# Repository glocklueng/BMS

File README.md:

# BMS
Battery management system

This is battery management system developed on University FESB for purpose of student project E-kart.
Features:
here goes features

Pic

Description

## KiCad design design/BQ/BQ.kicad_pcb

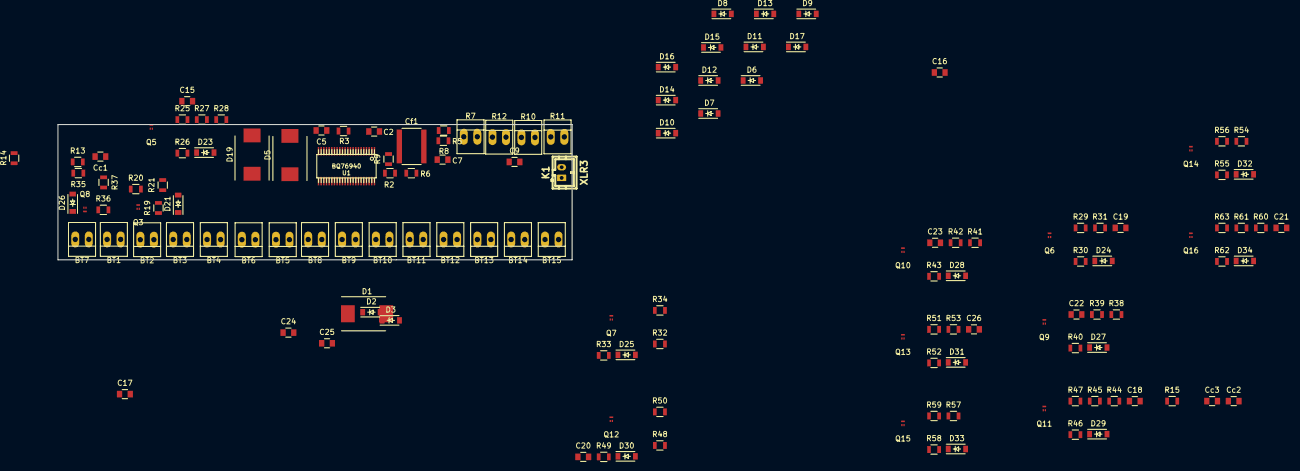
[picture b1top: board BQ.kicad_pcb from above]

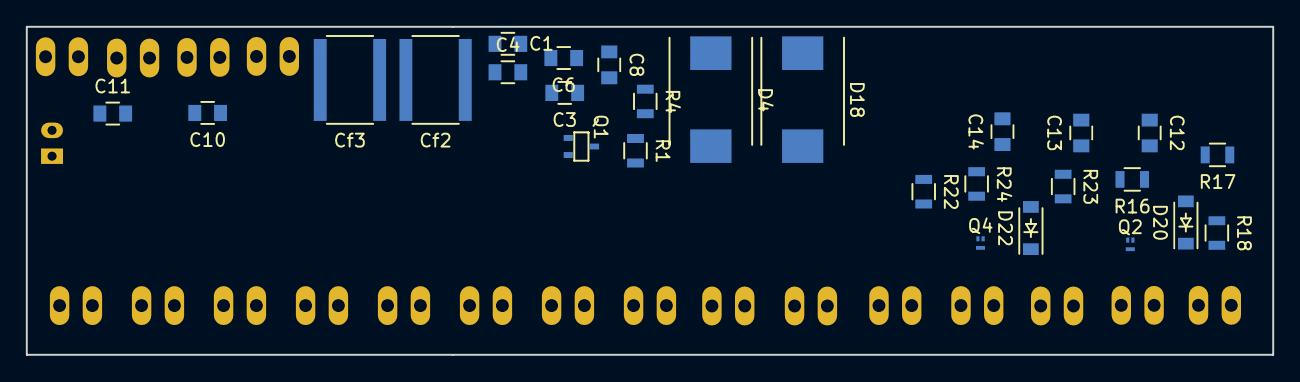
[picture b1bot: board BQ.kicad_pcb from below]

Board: 2 copper layers, 96.5 x 25.4 mm, 162 parts (27 on the bottom side), 87 nets, no tracks yet.

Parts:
BT1, BT2, BT3, BT4, BT5, BT6, BT7, BT8, BT9, BT10, BT11, BT12, BT13, BT14, BT15: BATTERY; PINHEAD1-2
C1, C9, C10, C11: 4.7; C_0805
C2, C4, C5: 1u; C_0805
C3, C6, C8: 0.1u; C_0805
C7: 4,7; C_0805
C12, C13, C14, C15, C16, C17, C18, C19, C20, C21, C22, C23, C24, C25, C26: 10u; C_0805
Cc1, Cc2: 10u; C_0805
Cc3: 1ou; C_0805
Cf1, Cf2, Cf3: 40u; C_1825
D1, D5, D18, D19: DIODE; Diode-DO-214AB
D2, D3: ZENER; SOD-123
D4: 100V; Diode-DO-214AB
D6, D7, D8, D9, D10, D11, D12, D13, D14, D15, D16, D17: DIODESCH; SOD-123
D20, D21, D22, D23, D24, D27, D28, D29, D31, D32, D33, D34: 5,6; SOD-123
D25, D26, D30: 5,6V; SOD-123
K1: XLR3; b2b-ph-kl
Q1: BST82,215; sc70
Q2, Q3, Q4, Q5, Q6, Q9, Q10, Q11, Q13, Q14, Q15, Q16: MOSFET_N; DFB1006-4
Q7, Q8, Q12: DMN2300UFB4-7B; DFB1006-4
R1: 200; R_0805
R2: 100k; R_0805
R3, R13, R14, R15, R18, R21, R24, R25, R28, R31, R34, R37, R40, R43, R44, R47, R50, R53, R56, R59, R60, R63: 1K; R_0805
R4: 100K; R_0805
R5, R6, R8: 100; R_0805
R7: SHUNT 0.001; PINHEAD1-2
R9: 300K; R_0805
R10, R11, R12: NTC 10k; PINHEAD1-2
R16, R19, R22, R26, R29, R32, R35, R38, R41, R45, R48, R51, R54, R57, R61: 50; R_0805
R17, R20, R23, R27, R30, R33, R36, R39, R42, R46, R49, R52, R55, R58, R62: 10K; R_0805
U1: BQ76940; AB2_TSSOP44_0p50P

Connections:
+BATT: BT15.1, R1.2, R3.2, R60.2, R61.1
-BATT_In: C1.2, C2.2, C3.2, C7.1, C8.2, C9.1, C18.1, Cc1.2, Cf1.1, R7.2, R9.2, R10.2, R13.1, R36.1, U1.3
/ALERT: R9.1, U1.44
/BATT: Cf3.2, D19.2, R3.1, U1.20
/Battery_pack/A: BT4.1, C4.1, C11.1, C17.1, Cc3.2, Cf1.2, Cf2.1, D5.2, D8.1, D9.1, D12.1, D13.1, D16.1, D17.1, R11.2, R15.1, R25.2, R26.1, R33.1, U1.10
/Battery_pack/B: BT10.1, BT11.1, BT12.2, C5.1, C10.1, Cc2.1, Cf2.2, Cf3.1, D6.1, D7.1, D10.1, D11.1, D14.1, D15.1, D18.2, D31.1, Q13.D, R2.2, R12.2, R14.1, R44.2, R45.1, R48.1, R53.2, U1.15
/Battery_pack/BattertyVC14-15/Battery cell/-B: BT15.2, D34.1, Q16.D, R63.2
/Battery_pack/Battery12-13/VC_0d: BT12.1, BT13.2, D32.1, Q14.D, R51.1, R56.2
/Battery_pack/BatteryVC0-1/Battery cell/-B: BT7.2, D26.1, Q8.D, R37.2
/Battery_pack/BatteryVC0-1/Rx: BT1.2, BT7.1, D20.1, Q2.D, R13.2, R18.2, R35.1
/Battery_pack/BatteryVC2-3/VC_0d: BT1.1, BT2.2, D21.1, Q3.D, R16.1, R21.2
/Battery_pack/BatteryVC3-4/VC_0d: BT2.1, BT3.2, D22.1, Q4.D, R19.1, R24.2
/Battery_pack/BatteryVC4-5/Battery cell/-B: BT4.2, D23.1, Q5.D, R28.2
/Battery_pack/BatteryVC5b-6/Battery cell/-B: BT6.2, D25.1, Q7.D, R34.2
/Battery_pack/BatteryVC5b-6/Rx: BT6.1, R15.2, R32.1
/Battery_pack/BatteryVC6-7/VC_0d: BT5.2, D24.1, Q6.D, R31.2
/Battery_pack/BatteryVC7-8/VC_0d: BT5.1, BT8.2, D27.1, Q9.D, R29.1, R40.2
/Battery_pack/BatteryVC8-9/VC_0d: BT8.1, BT9.2, D28.1, Q10.D, R38.1, R43.2
/Battery_pack/BatteryVC9-10/Battery cell/-B: BT10.2, D29.1, Q11.D, R47.2
/Battery_pack/BatteryVC10B-11/Battery cell/-B: BT11.2, D30.1, Q12.D, R50.2
/Battery_pack/BatteryVC10B-11/VC0_cap: C22.1, R14.2, R49.1
/Battery_pack/BatteryVC13-14/VC_0d: BT13.1, BT14.2, D33.1, Q15.D, R54.1, R59.2
/Battery_pack/VC0: Cc1.1, R37.1, U1.41
/Battery_pack/VC1: C12.1, C18.2, R17.1, R18.1, U1.40
/Battery_pack/VC2: C12.2, C13.1, R20.1, R21.1, U1.39
/Battery_pack/VC3: C13.2, C14.1, R23.1, R24.1, U1.38
/Battery_pack/VC4: BT3.1, C14.2, C15.1, R22.1, R27.1, R28.1, U1.37
/Battery_pack/VC5: C15.2, D5.1, R25.1, U1.36
/Battery_pack/VC5b: Cc3.1, D8.2, R34.1, U1.35
/Battery_pack/VC6: C16.1, C17.2, D12.2, R30.1, R31.1, U1.34
/Battery_pack/VC7: C16.2, C19.1, D16.2, R39.1, R40.1, U1.33
/Battery_pack/VC8: C19.2, C20.1, D9.2, R42.1, R43.1, U1.32
/Battery_pack/VC9: BT9.1, C20.2, C21.1, D13.2, R41.1, R46.1, R47.1, U1.31
/Battery_pack/VC10: C21.2, D17.2, D18.1, R44.1, U1.30
/Battery_pack/VC10b: Cc2.2, D15.2, R50.1, U1.29
/Battery_pack/VC11: C22.2, C23.1, D11.2, R52.1, R53.1, U1.28
/Battery_pack/VC12: C23.2, C24.1, D7.2, R55.1, R56.1, U1.27
/Battery_pack/VC13: C24.2, C25.1, D6.2, R58.1, R59.1, U1.26
/Battery_pack/VC14: BT14.1, C25.2, C26.1, D10.2, R57.1, R62.1, R63.1, U1.25
/Battery_pack/VC15: C26.2, D14.2, D19.1, R60.1, U1.24
/CHG: K1.1, U1.2
/DSG: K1.2, U1.1
/NTC Temp monitor/Temp1_in: C9.2, R10.1, U1.6
/NTC Temp monitor/Temp2_in: C11.2, R11.1, U1.13
/NTC Temp monitor/Temp3_in: C10.2, R12.1, U1.18
/Vcc: C1.1, U1.8
unnamed: C2.1, U1.7
unnamed: C3.1, C6.2, R5.1, U1.42
unnamed: C4.2, U1.11, U1.12, U1.14
unnamed: C5.2, U1.16, U1.17, U1.19
unnamed: C6.1, C8.1, R8.1, U1.43
unnamed: C7.2, R6.2, U1.9
unnamed: D1.1, D3.2, D4.1, Q1.S, R4.1
unnamed: D1.2, Q1.D, R1.1
unnamed: D2.1, D3.1
unnamed: D2.2, Q1.G, R2.1
unnamed: D4.2, R4.2, R6.1
unnamed: D20.2, Q2.G, R17.2
unnamed: D21.2, Q3.G, R20.2
unnamed: D22.2, Q4.G, R23.2
unnamed: D23.2, Q5.G, R27.2
unnamed: D24.2, Q6.G, R30.2
unnamed: D25.2, Q7.G, R33.2
unnamed: D26.2, Q8.G, R36.2
unnamed: D27.2, Q9.G, R39.2
unnamed: D28.2, Q10.G, R42.2
unnamed: D29.2, Q11.G, R46.2
unnamed: D30.2, Q12.G, R49.2
unnamed: D31.2, Q13.G, R52.2
unnamed: D32.2, Q14.G, R55.2
unnamed: D33.2, Q15.G, R58.2
unnamed: D34.2, Q16.G, R62.2
unnamed: Q2.S, R16.2
unnamed: Q3.S, R19.2
unnamed: Q4.S, R22.2
unnamed: Q5.S, R26.2
unnamed: Q6.S, R29.2
unnamed: Q7.S, R32.2
unnamed: Q8.S, R35.2
unnamed: Q9.S, R38.2
unnamed: Q10.S, R41.2
unnamed: Q11.S, R45.2
unnamed: Q12.S, R48.2
unnamed: Q13.S, R51.2
unnamed: Q14.S, R54.2
unnamed: Q15.S, R57.2
unnamed: Q16.S, R61.2

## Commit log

2001-01-01 Edit TODO fix README and add Disclamer in datasheet and add gitignore
2001-01-01 Remove .bak files so dir is not cluttered
2001-01-01 Just help file for other
2001-01-01 Just for help to other
2001-01-01 Revert "Remove .bak files so dir is not cluttered"
    This reverts commit 8636d5cb2d588337d3320b2edcf361f075b09c5a.
2001-01-01 Just helping others
2001-01-01 Fix BQ scheme so it's more readable
2001-01-01 Add a cell to 10 but currently a scheme is a total mess fix it
2015-07-31 First commit start by adding basic sheets and some datasheets
2015-07-31 More specifed TODO stuff
2015-07-31 Add new component bq and other libs also fix lib path. Project is now portable
2015-07-31 README and TODO fix
2015-08-01 Fix lib and add missing dataseet document
2015-08-01 Add new files
2015-08-01 Some modification and started job
2015-08-02 Some small fix in BQ and TODO
2015-08-03 TODO,add pdf(schematic)
2015-08-05 Renew pdf set some vaules add links and more comments
2015-08-07 Add folder pictures and put some pictures in it
2015-08-07 Fix schematic so its more readable (I think so)
2015-08-24 Add new example in datasheet define more values
2015-08-24 Update pdf
2015-08-25 Fix some schematic update pdf
2015-08-25 Fix some mistakes and some explanations
2015-08-27 MCU datasheet
2015-11-29 Add a new BQ and start routing board for (reason for separation for easier routing) but in the end I souldnt do this becasue of netlist but its ok because of symlink
2015-12-08 Add datasheets
2015-12-08 Start autorouting and palcing a components
